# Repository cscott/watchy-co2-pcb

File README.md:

watchy-co2-pcb
==============
A small 10.3mm x 17mm PCB to mount the
[Sensirion SCD40/41 CO₂ sensor](https://www.sensirion.com/en/environmental-sensors/carbon-dioxide-sensors/carbon-dioxide-sensor-scd4x/)
on.  It contains footprints to optionally add a
[3.3v LDO regulator](https://www.njr.com/electronic_device/PDF/NJM2881_NJM2882_E.pdf)
and some extra capacitors to better decouple the
power supply.

This board is designed to be used with the
[Watchy](https://watchy.sqfmi.com/) Open Source E-Paper Watch.
A matching case can be found at
[cscott/watchy-co2-case](https://github.com/cscott/watchy-co2-case#readme),
and a watchface using this board can be found at
[cscott/watchy-c4](https://github.com/cscott/watchy-c4#readme),

When wiring to Watchy, the SCL/SDA/GND inputs should be wired to the
appropriate test points on the Watchy PCB back, as shown below.

For Vin, there are three options:

1. The Vin input can be connected to the +3V3 test point above, with
JP1 in its default UNREG position.  This shares the 3.3V power supply
with the main ESP32.  It may (or may not) be too noisy for best SCD40
accuracy.

2. The Vin input can be connected directly to the battery +BATT at
one of the positions highlighted in pink below. JP1 would be left in
its default UNREG position.  This provides the best battery efficiency
(the SCD40 can tolerate the higher voltage level), but (depending on
the battery internal resistance) again may be too noisy for best SCD40
accuracy.  However, this is the configuration I have used in the watches
I've assembled.

3. The Vin input can be connected directly to the battery +BATT as
above, and JP1 moved to its alternate REG position.  This powers the
SCD40 by its own dedicated LDO regulator, ensuring the quietest
possible power supply.  In this configuration you can swap JP2 as well
to its GPIO0 position and wire up the GPIO0 input to control the power
to the SCD40.  See the pink highlight below for the test point location
which provides access to GPIO0.

The CP1 and CP3 capacitors will provide useful decoupling in all three
configurations, although (depending on noise measurements) they may
not be required.  All three capacitors and U2 are required in
configuration three.

Here's a [digikey link](https://www.digikey.com/short/t87dq9r9) for all
components.

Note that this board will work with the lower-cost SCD40 sensor, and gets
about a day of battery life in this configuration with the stock Watchy
battery, reading CO₂ levels every 30 seconds.  The slightly more expensive
SCD41 sensor has the exact same pinout and footprint, but contains a
lower-power mode where it can read the sensor every 5 minutes instead,
and power consumption drops from 3.2mA to 0.5mA. (In October 2021 the SCD42
was added to the product lineup which is also footprint-compatible, but
this part drops the low power modes and requires 15mA which would make
it incompatible with wearable use.)

This board was designed using [KiCad 5](https://www.kicad.org/).

(See also [this doc from TI](https://www.ti.com/lit/an/scaa048/scaa048.pdf)
on decoupling techniques using a ferrite bead if further noise reduction
is necessary.  The
[Sensirion datasheet for the SCD40](https://www.sensirion.com/fileadmin/user_upload/customers/sensirion/Dokumente/9.5_CO2/Sensirion_CO2_Sensors_SCD4x_Datasheet.pdf) suggests less than 30mV of power supply noise.)

### More photos of installed board

Note that I've connected GPIO in these photos, even though I'm not using
regulator (I'm using power option 2).  I also added an extra capacitor,
whose high side is *supposed* to be connected to pins 5 and 6 of the CP2104
to fix the dreaded "USB death" problem of the first release of the Watchy,
but instead (due to a confusion I had about the `PWR_FLAG` symbol on the
Watchy schematic, it's connected across the input to U2, the watchy voltage
regulator -- which could *also* use a capacitor to stabilize the regulator,
but wasn't what I was intending to do...

I also had issues with the watchy button switches popping open because
they are not supported on the bottom side; the orangish bits of
plastic in these photos are my impromptu shims to allow the bottom
side of the switches to be supported by the bottom case half.

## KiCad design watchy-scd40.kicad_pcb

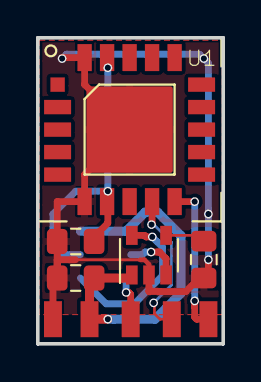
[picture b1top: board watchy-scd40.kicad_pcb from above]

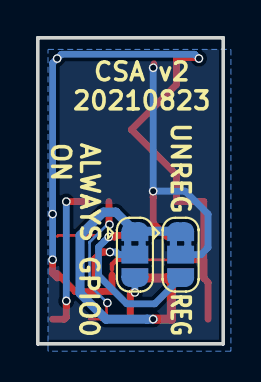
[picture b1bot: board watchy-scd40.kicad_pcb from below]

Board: 2 copper layers, 10.3 x 17.0 mm, 12 parts (2 on the bottom side), 9 nets.

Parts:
C1: .1uF; C_0805_2012Metric_Pad1.15x1.40mm_HandSolder
C2: .01uF; C_0805_2012Metric_Pad1.15x1.40mm_HandSolder
C3: 1uF; C_0805_2012Metric_Pad1.15x1.40mm_HandSolder
JP1: V SELECT; SolderJumper-3_P1.3mm_Bridged2Bar12_RoundedPad1.0x1.5mm
JP2: EN SEL; SolderJumper-3_P1.3mm_Bridged2Bar12_RoundedPad1.0x1.5mm
TP1, TP2, TP3, TP4, TP5: TestPoint; TestPoint_Pad_2.0x2.0mm-nosilk
U1: SCD40-D-R2
U2: NJM2882F33; SOT-23-5

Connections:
GND: C1.2, C2.2, C3.2, TP5.1, U1.6, U1.20, U1.21, U2.2
GPIO0: JP2.3, TP2.1
unnamed: C2.1, U2.4
unnamed: C3.1, JP1.2, U1.7, U1.19
unnamed: JP1.3, U2.5
unnamed: JP2.2, U2.3
SCL: TP3.1, U1.9
SDA: TP4.1, U1.10
Vin: C1.1, JP1.1, JP2.1, TP1.1, U2.1

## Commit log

2021-08-27 v2: Tweaks to soldermask and to silkscreen
2021-08-27 Add a tiny bit of documentation and some renders
2021-08-27 Improve README; fix visibility of component labels on silkscreen layer
2021-08-27 Additional links in the README
2021-08-27 Add digikey cart link
2021-08-27 More documentation of proper wiring and possible configurations
2021-08-27 More documentation updates
2021-08-27 More docs & links
2021-10-27 Add some photos
2021-10-27 Improve readme, add more photos
2021-10-27 Reorder first two photos
2021-10-27 Start with a hero shot
